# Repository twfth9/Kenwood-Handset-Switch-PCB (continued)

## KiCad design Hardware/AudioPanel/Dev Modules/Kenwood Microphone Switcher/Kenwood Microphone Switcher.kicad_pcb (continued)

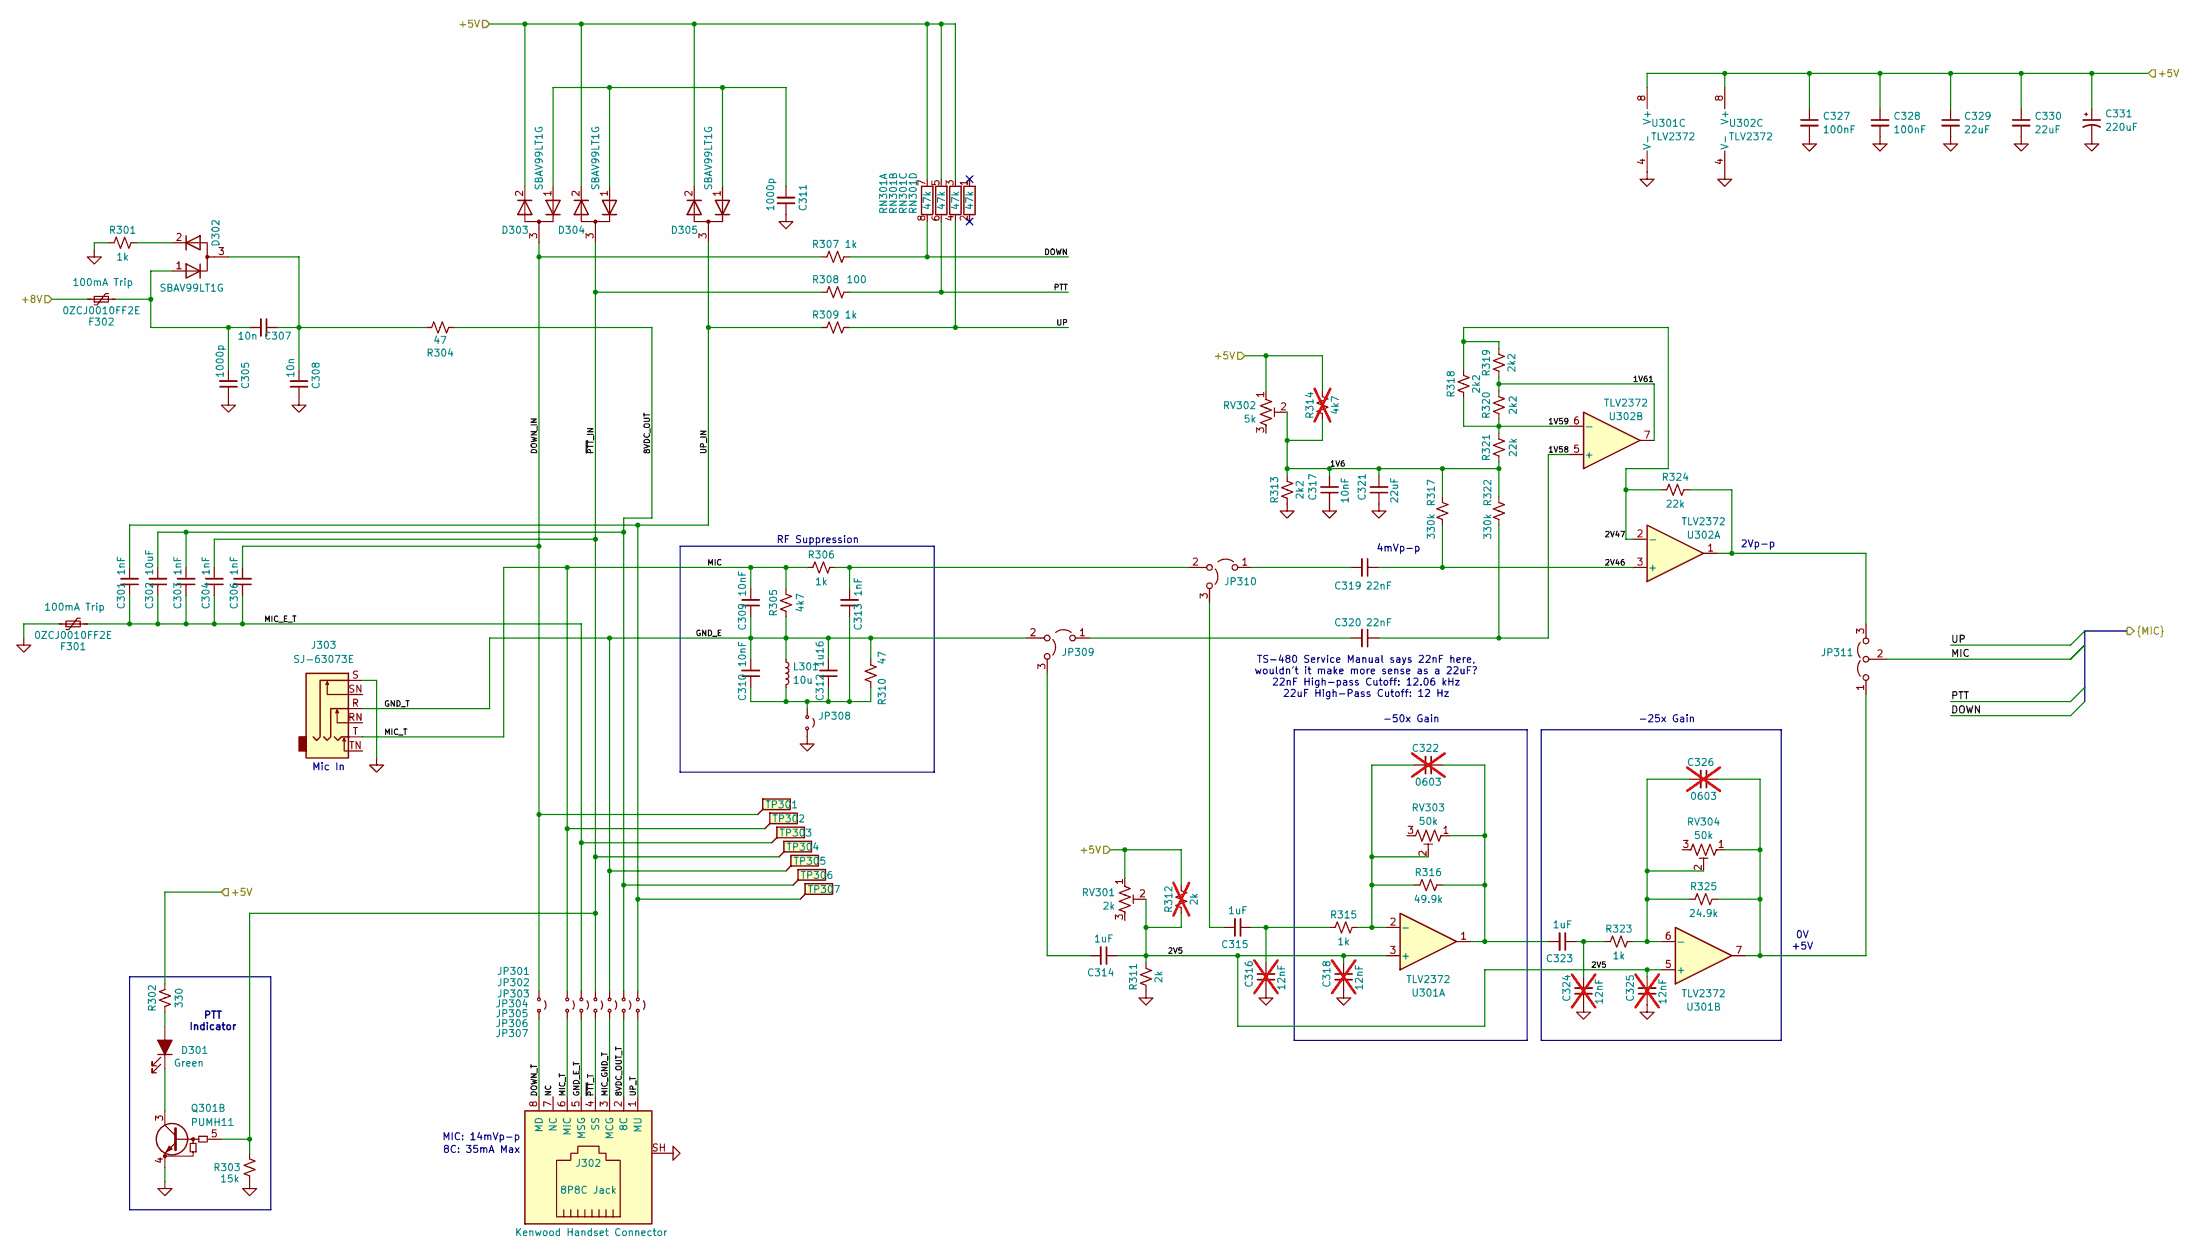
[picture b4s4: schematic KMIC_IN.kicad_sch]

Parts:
C301, C303, C304, C306, C313: 1nF; C_0402_1005Metric
C302: 10uF; C_0603_1608Metric
C305, C311: 1000p; C_0402_1005Metric
C307, C308: 10n; C_0402_1005Metric
C309, C310, C317: 10nF; C_0402_1005Metric
C312: 1u16; C_0603_1608Metric
C314, C315: 1uF; C_0603_1608Metric
C316, C318, C324, C325: 12nF; C_0402_1005Metric; not fitted
C319, C320: 22nF; C_0402_1005Metric
C321, C329, C330: 22uF; C_0603_1608Metric
C322, C326: 0603; C_0603_1608Metric; not fitted
C323: 1uF; C_0402_1005Metric
C327, C328: 100nF; C_0402_1005Metric
C331: 220uF; CP_Elec_10x10
D301: Green; LED_0603_1608Metric; DigiKey Part Number 732-5016-ND
D302, D303, D304, D305: SBAV99LT1G; SOT-23
F301, F302: 0ZCJ0010FF2E; Fuse_1206_3216Metric
J302: 8P8C Jack; Mystery_RJ45
J303: SJ-63073E; CUI_SJ-63073E
JP301, JP302, JP303, JP304, JP305, JP306, JP307, JP308: Jumper_2_Small_Open; SolderJumper-2_P1.3mm_Open_Pad1.0x1.5mm
JP309, JP310, JP311: Jumper_3_Open; SolderBridge_3L
L301: 10u; L_0805_2012Metric
Q301: PUMH11; SOT363_NXP
R301, R306, R307, R309, R315, R323: 1k; R_0402_1005Metric
R302: 330; R_0402_1005Metric
R303: 15k; R_0402_1005Metric
R304, R310: 47; R_0402_1005Metric
R305: 4k7; R_0402_1005Metric
R308: 100; R_0402_1005Metric
R311: 2k; R_0402_1005Metric
R312: 2k; R_0402_1005Metric; not fitted
R313, R318, R319, R320: 2k2; R_0402_1005Metric
R314: 4k7; R_0402_1005Metric; not fitted
R316: 49.9k; R_0402_1005Metric
R317, R322: 330k; R_0402_1005Metric
R321, R324: 22k; R_0402_1005Metric
R325: 24.9k; R_0402_1005Metric
RN301: 47k; R_Array_Convex_4x1206
RV301: 2k; Potentiometer_Bourns_TC33X_Vertical
RV302: 5k; Potentiometer_Bourns_TC33X_Vertical
RV303, RV304: 50k; Potentiometer_Bourns_TC33X_Vertical
TP301, TP302, TP303, TP304, TP305, TP306, TP307: TestPoint_Flag; KEYSTONE_5017
U301, U302: TLV2372; SOIC-8_3.9x4.9mm_P1.27mm

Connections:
/+5V_CODRIVER: C327.1, C328.1, C329.1, C330.1, C331.1, D303.2 (K), D304.2 (K), D305.2 (K), R302.2, R312.1, R314.1, RN301.3, RN301.5, RN301.7, RV301.1, RV302.1, U301.8 (V+), U302.8 (V+); also elsewhere on the board
/+8V_CODRIVER: F302.1; also elsewhere on the board
/CODRIVER_MIC.DOWN: R307.1, RN301.8
/CODRIVER_MIC.MIC: C309.2, J302.6 (MIC), J303.T, JP302.1 (A), JP302.2 (B), JP311.2 (C), R305.1, R306.2, TP302.1; also elsewhere on the board
/CODRIVER_MIC.PTT: R308.1, RN301.6; also elsewhere on the board
/CODRIVER_MIC.UP: R309.1, RN301.4; also elsewhere on the board
/CoDriver MIC Input/1V6: C317.2, C321.2, R313.1, R314.2, R317.1, R321.2, R322.1, RV302.2
/CoDriver MIC Input/1V58: C320.1, R322.2, U302.5 (+)
/CoDriver MIC Input/1V59: R318.2, R320.2, R321.1, U302.6 (-)
/CoDriver MIC Input/1V61: R319.2, R320.1, U302.7
/CoDriver MIC Input/2V5: C314.1, C318.2, C325.2, R311.1, R312.2, RV301.2, U301.3 (+), U301.5 (+)
/CoDriver MIC Input/2V46: C319.1, R317.2, U302.3 (+)
/CoDriver MIC Input/2V47: R318.1, R319.1, R324.2, U302.2 (-)
/CoDriver MIC Input/8VDC_OUT: C302.2, C303.2, JP306.1 (A), R304.2, TP306.1
/CoDriver MIC Input/8VDC_OUT_T: J302.2 (8C), JP306.2 (B)
/CoDriver MIC Input/DOWN_IN: C306.2, D303.3 (common), JP301.1 (A), R307.2, TP301.1
/CoDriver MIC Input/DOWN_T: J302.8 (MD), JP301.2 (B)
/CoDriver MIC Input/GND_E: C309.1, C310.2, C312.2, J303.R, JP305.1 (A), JP309.2 (C), L301.1, R305.2, R310.1, TP305.1
/CoDriver MIC Input/GND_E_T: J302.5 (MSG), JP303.2 (B)
/CoDriver MIC Input/MIC_E_T: C301.1, C302.1, C303.1, C304.1, C306.1, F301.2, JP303.1 (A), TP303.1
/CoDriver MIC Input/MIC_GND_T: J302.3 (MCG), JP305.2 (B)
/CoDriver MIC Input/NC: J302.7 (NC)
/CoDriver MIC Input/UP_IN: C301.2, D305.3 (common), JP307.1 (A), R309.2, TP307.1
/CoDriver MIC Input/UP_T: J302.1 (MU), JP307.2 (B)
/CoDriver MIC Input/~PTT_IN: C304.2, D304.3 (common), JP304.1 (A), Q301.5 (B2), R303.1, R308.2, TP304.1
/CoDriver MIC Input/~PTT_T: J302.4 (SS), JP304.2 (B)
/Driver MIC Input/~PTT_IN: Q301.2 (B1); also elsewhere on the board
GND: C305.1, C308.1, C311.1, C316.1, C317.1, C318.1, C321.1, C324.1, C325.1, C327.2, C328.2, C329.2, C330.2, C331.2, F301.1, J302.SH, J303.S, JP308.2 (B), Q301.1 (E1), Q301.4 (E2), R301.2, R303.2, R311.2, R313.2, U301.4 (V-), U302.4 (V-); also elsewhere on the board
unnamed: C315.1, C316.2, R315.2
unnamed: C322.1, C323.2, R316.1, RV303.1, U301.1
unnamed: C323.1, C324.2, R323.2
unnamed: D301.2 (A), R302.1
unnamed: D301.1 (K), Q301.3 (C2)
unnamed: C305.2, C307.2, D302.1 (A), F302.2
unnamed: D302.2 (K), R301.1
unnamed: C307.1, C308.2, D302.3 (common), R304.1
unnamed: C311.2, D303.1 (A), D304.1 (A), D305.1 (A)
unnamed 278: Q301.6 (C1); also elsewhere on the board
unnamed: C310.1, C312.1, C313.1, JP308.1 (A), L301.2, R310.2
unnamed: C320.2, JP309.1 (A)
unnamed: C314.2, JP309.3 (B)
unnamed: C319.2, JP310.1 (A)
unnamed: C315.2, JP310.3 (B)
unnamed: C313.2, JP310.2 (C), R306.1
unnamed: C326.1, JP311.1 (A), R325.1, RV304.1, U301.7
unnamed: JP311.3 (B), R324.1, U302.1
unnamed: C322.2, R315.1, R316.2, RV303.2, U301.2 (-)
unnamed: C326.2, R323.1, R325.2, RV304.2, U301.6 (-)

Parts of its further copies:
C401, C403, C404, C406, C413: 1nF; C_0402_1005Metric
C402: 10uF; C_0603_1608Metric
C405, C411: 1000p; C_0402_1005Metric
C407, C408: 10n; C_0402_1005Metric
C409, C410, C417: 10nF; C_0402_1005Metric
C412: 1u16; C_0603_1608Metric
C414, C415: 1uF; C_0603_1608Metric
C416, C418, C424, C425: 12nF; C_0402_1005Metric; not fitted
C419, C420: 22nF; C_0402_1005Metric
C421, C429, C430: 22uF; C_0603_1608Metric
C422, C426: 0603; C_0603_1608Metric; not fitted
C423: 1uF; C_0402_1005Metric
C427, C428: 100nF; C_0402_1005Metric
C431: 220uF; CP_Elec_10x10
D401: Green; LED_0603_1608Metric; DigiKey Part Number 732-5016-ND
D402, D403, D404, D405: SBAV99LT1G; SOT-23
F401, F402: 0ZCJ0010FF2E; Fuse_1206_3216Metric
J402: 8P8C Jack; Mystery_RJ45
J403: SJ-63073E; CUI_SJ-63073E
JP401, JP402, JP403, JP404, JP405, JP406, JP407, JP408: Jumper_2_Small_Open; SolderJumper-2_P1.3mm_Open_Pad1.0x1.5mm
JP409, JP410, JP411: Jumper_3_Open; SolderBridge_3L
L401: 10u; L_0805_2012Metric
R401, R406, R407, R409, R415, R423: 1k; R_0402_1005Metric
R402: 330; R_0402_1005Metric
R403: 15k; R_0402_1005Metric
R404, R410: 47; R_0402_1005Metric
R405: 4k7; R_0402_1005Metric
R408: 100; R_0402_1005Metric
R411: 2k; R_0402_1005Metric
R412: 2k; R_0402_1005Metric; not fitted
R413, R418, R419, R420: 2k2; R_0402_1005Metric
R414: 4k7; R_0402_1005Metric; not fitted
R416: 49.9k; R_0402_1005Metric
R417, R422: 330k; R_0402_1005Metric
R421, R424: 22k; R_0402_1005Metric
R425: 24.9k; R_0402_1005Metric
RN401: 47k; R_Array_Convex_4x1206
RV401: 2k; Potentiometer_Bourns_TC33X_Vertical
RV402: 5k; Potentiometer_Bourns_TC33X_Vertical
RV403, RV404: 50k; Potentiometer_Bourns_TC33X_Vertical
TP401, TP402, TP403, TP404, TP405, TP406, TP407: TestPoint_Flag; KEYSTONE_5017
U401, U402: TLV2372; SOIC-8_3.9x4.9mm_P1.27mm

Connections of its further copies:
/+5V_DRIVER: C427.1, C428.1, C429.1, C430.1, C431.1, D403.2 (K), D404.2 (K), D405.2 (K), R402.2, R412.1, R414.1, RN401.3, RN401.5, RN401.7, RV401.1, RV402.1, U401.8 (V+), U402.8 (V+); also elsewhere on the board
/+8V_DRIVER: F402.1; also elsewhere on the board
/DRIVER_MIC.DOWN: R407.1, RN401.8
/DRIVER_MIC.MIC: C409.2, J402.6 (MIC), J403.T, JP402.1 (A), JP402.2 (B), JP411.2 (C), R405.1, R406.2, TP402.1; also elsewhere on the board
/DRIVER_MIC.PTT: R408.1, RN401.6; also elsewhere on the board
/DRIVER_MIC.UP: R409.1, RN401.4; also elsewhere on the board
/Driver MIC Input/1V6: C417.2, C421.2, R413.1, R414.2, R417.1, R421.2, R422.1, RV402.2
/Driver MIC Input/1V58: C420.1, R422.2, U402.5 (+)
/Driver MIC Input/1V59: R418.2, R420.2, R421.1, U402.6 (-)
/Driver MIC Input/1V61: R419.2, R420.1, U402.7
/Driver MIC Input/2V5: C414.1, C418.2, C425.2, R411.1, R412.2, RV401.2, U401.3 (+), U401.5 (+)
/Driver MIC Input/2V46: C419.1, R417.2, U402.3 (+)
/Driver MIC Input/2V47: R418.1, R419.1, R424.2, U402.2 (-)
/Driver MIC Input/8VDC_OUT: C402.2, C403.2, JP406.1 (A), R404.2, TP406.1
/Driver MIC Input/8VDC_OUT_T: J402.2 (8C), JP406.2 (B)
/Driver MIC Input/DOWN_IN: C406.2, D403.3 (common), JP401.1 (A), R407.2, TP401.1
/Driver MIC Input/DOWN_T: J402.8 (MD), JP401.2 (B)
/Driver MIC Input/GND_E: C409.1, C410.2, C412.2, J403.R, JP405.1 (A), JP409.2 (C), L401.1, R405.2, R410.1, TP405.1
/Driver MIC Input/GND_E_T: J402.5 (MSG), JP403.2 (B)
/Driver MIC Input/MIC_E_T: C401.1, C402.1, C403.1, C404.1, C406.1, F401.2, JP403.1 (A), TP403.1
/Driver MIC Input/MIC_GND_T: J402.3 (MCG), JP405.2 (B)
/Driver MIC Input/NC: J402.7 (NC)
/Driver MIC Input/UP_IN: C401.2, D405.3 (common), JP407.1 (A), R409.2, TP407.1
/Driver MIC Input/UP_T: J402.1 (MU), JP407.2 (B)
/Driver MIC Input/~PTT_IN: C404.2, D404.3 (common), JP404.1 (A), R403.1, R408.2, TP404.1; also elsewhere on the board
/Driver MIC Input/~PTT_T: J402.4 (SS), JP404.2 (B)
GND: C405.1, C408.1, C411.1, C416.1, C417.1, C418.1, C421.1, C424.1, C425.1, C427.2, C428.2, C429.2, C430.2, C431.2, F401.1, J402.SH, J403.S, JP408.2 (B), R401.2, R403.2, R411.2, R413.2, U401.4 (V-), U402.4 (V-); also elsewhere on the board
unnamed: C415.1, C416.2, R415.2
unnamed: C422.1, C423.2, R416.1, RV403.1, U401.1
unnamed: C423.1, C424.2, R423.2
unnamed: D401.2 (A), R402.1
unnamed 278: D401.1 (K); also elsewhere on the board
unnamed: C405.2, C407.2, D402.1 (A), F402.2
unnamed: D402.2 (K), R401.1
unnamed: C407.1, C408.2, D402.3 (common), R404.1
unnamed: C411.2, D403.1 (A), D404.1 (A), D405.1 (A)
unnamed: C410.1, C412.1, C413.1, JP408.1 (A), L401.2, R410.2
unnamed: C420.2, JP409.1 (A)
unnamed: C414.2, JP409.3 (B)
unnamed: C419.2, JP410.1 (A)
unnamed: C415.2, JP410.3 (B)
unnamed: C413.2, JP410.2 (C), R406.1
unnamed: C426.1, JP411.1 (A), R425.1, RV404.1, U401.7
unnamed: JP411.3 (B), R424.1, U402.1
unnamed: C422.2, R415.1, R416.2, RV403.2, U401.2 (-)
unnamed: C426.2, R423.1, R425.2, RV404.2, U401.6 (-)

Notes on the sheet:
MIC: 14mVp-p
RF Suppression
-50x Gain
4mVp-p
PTT Indicator
-25x Gain
TS-480 Service Manual says 22nF here, wouldn't it make more sense as a 22uF? 22nF High-pass Cutoff: 12.06 kHz 22uF High-Pass Cutoff: 12 Hz
Mic In
0V +5V
8C: 35mA Max
2Vp-p

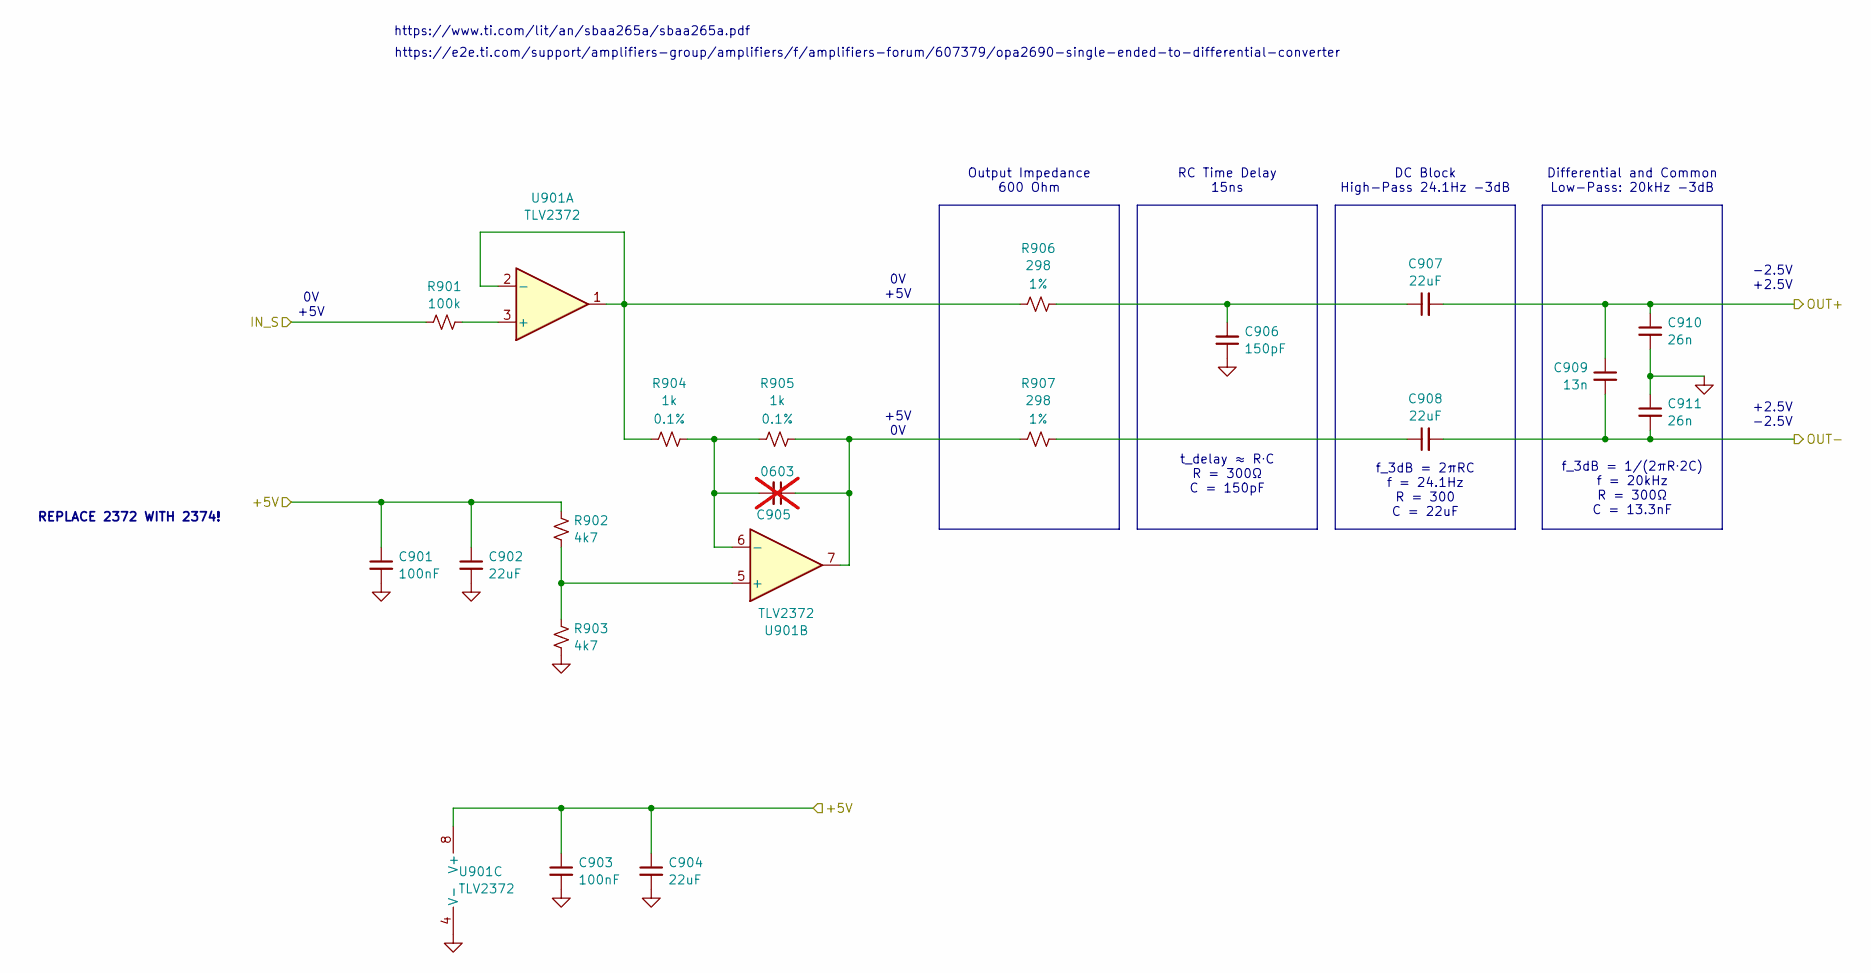
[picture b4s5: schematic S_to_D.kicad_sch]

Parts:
C901, C903: 100nF; C_0402_1005Metric
C902, C904, C907, C908: 22uF; C_0603_1608Metric
C905: 0603; C_0603_1608Metric; not fitted
C906: 150pF; C_0402_1005Metric
C909: 13n; C_0402_1005Metric
C910, C911: 26n; C_0402_1005Metric
R901: 100k; R_0402_1005Metric
R902, R903: 4k7; R_0402_1005Metric
R904, R905: 1k; R_0402_1005Metric; Tolerance 0.1%
R906, R907: 298; R_0402_1005Metric; Tolerance 1%
U901: TLV2372; SOIC-8_3.9x4.9mm_P1.27mm

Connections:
/+5V_MIC_480: C901.1, C902.1, C903.1, C904.1, R902.2, U901.8 (V+); also elsewhere on the board
/TS-480 MIC Output/MIC+: C907.2, C909.1, C910.1; also elsewhere on the board
/TS-480 MIC Output/MIC-: C908.2, C909.2, C911.2; also elsewhere on the board
/TS-480 MIC Output/Single to Differential/IN_S: R901.1; also elsewhere on the board
GND: C901.2, C902.2, C903.2, C904.2, C906.1, C910.2, C911.1, R903.1, U901.4 (V-); also elsewhere on the board
unnamed: C905.1, R905.2, R907.1, U901.7
unnamed: C906.2, C907.1, R906.2
unnamed: C908.1, R907.2
unnamed: R901.2, U901.3 (+)
unnamed: R904.1, R906.1, U901.1, U901.2 (-)
unnamed: R902.1, R903.2, U901.5 (+)
unnamed: C905.2, R904.2, R905.1, U901.6 (-)

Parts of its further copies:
C1001, C1003, C1101, C1103, C1201, C1203: 100nF; C_0402_1005Metric
C1002, C1004, C1007, C1008, C1102, C1104, C1107, C1108, C1202, C1204, C1207, C1208: 22uF; C_0603_1608Metric
C1005, C1105, C1205: 0603; C_0603_1608Metric; not fitted
C1006, C1106, C1206: 150pF; C_0402_1005Metric
C1009, C1109, C1209: 13n; C_0402_1005Metric
C1010, C1011, C1110, C1111, C1210, C1211: 26n; C_0402_1005Metric
R1001, R1101, R1201: 100k; R_0402_1005Metric
R1002, R1003, R1102, R1103, R1202, R1203: 4k7; R_0402_1005Metric
R1004, R1005, R1104, R1105, R1204, R1205: 1k; R_0402_1005Metric; Tolerance 0.1%
R1006, R1007, R1106, R1107, R1206, R1207: 298; R_0402_1005Metric; Tolerance 1%
U1001, U1101, U1201: TLV2372; SOIC-8_3.9x4.9mm_P1.27mm

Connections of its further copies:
/+5V_MIC_700: C1101.1, C1102.1, C1103.1, C1104.1, R1102.2, U1101.8 (V+); also elsewhere on the board
/+5V_MIC_710: C1001.1, C1002.1, C1003.1, C1004.1, R1002.2, U1001.8 (V+); also elsewhere on the board
/+5V_MIC_EXTRA: C1201.1, C1202.1, C1203.1, C1204.1, R1202.2, U1201.8 (V+); also elsewhere on the board
/D-700 MIC Output/MIC+: C1107.2, C1109.1, C1110.1; also elsewhere on the board
/D-700 MIC Output/MIC-: C1108.2, C1109.2, C1111.2; also elsewhere on the board
/D-700 MIC Output/Single to Differential/IN_S: R1101.1; also elsewhere on the board
/D-710 MIC Output/MIC+: C1007.2, C1009.1, C1010.1; also elsewhere on the board
/D-710 MIC Output/MIC-: C1008.2, C1009.2, C1011.2; also elsewhere on the board
/D-710 MIC Output/Single to Differential/IN_S: R1001.1; also elsewhere on the board
/EXTRA MIC Output/MIC+: C1207.2, C1209.1, C1210.1; also elsewhere on the board
/EXTRA MIC Output/MIC-: C1208.2, C1209.2, C1211.2; also elsewhere on the board
/EXTRA MIC Output/Single to Differential/IN_S: R1201.1; also elsewhere on the board
GND: C1001.2, C1002.2, C1003.2, C1004.2, C1006.1, C1010.2, C1011.1, C1101.2, C1102.2, C1103.2, C1104.2, C1106.1, C1110.2, C1111.1, C1201.2, C1202.2, C1203.2, C1204.2, C1206.1, C1210.2, C1211.1, R1003.1, R1103.1, R1203.1, U1001.4 (V-), U1101.4 (V-), U1201.4 (V-); also elsewhere on the board
unnamed: C1005.1, R1005.2, R1007.1, U1001.7
unnamed: C1006.2, C1007.1, R1006.2
unnamed: C1008.1, R1007.2
unnamed: C1105.1, R1105.2, R1107.1, U1101.7
unnamed: C1106.2, C1107.1, R1106.2
unnamed: C1108.1, R1107.2
unnamed: C1205.1, R1205.2, R1207.1, U1201.7
unnamed: C1206.2, C1207.1, R1206.2
unnamed: C1208.1, R1207.2
unnamed: R1001.2, U1001.3 (+)
unnamed: R1004.1, R1006.1, U1001.1, U1001.2 (-)
unnamed: R1002.1, R1003.2, U1001.5 (+)
unnamed: C1005.2, R1004.2, R1005.1, U1001.6 (-)
unnamed: R1101.2, U1101.3 (+)
unnamed: R1104.1, R1106.1, U1101.1, U1101.2 (-)
unnamed: R1102.1, R1103.2, U1101.5 (+)
unnamed: C1105.2, R1104.2, R1105.1, U1101.6 (-)
unnamed: R1201.2, U1201.3 (+)
unnamed: R1204.1, R1206.1, U1201.1, U1201.2 (-)
unnamed: R1202.1, R1203.2, U1201.5 (+)
unnamed: C1205.2, R1204.2, R1205.1, U1201.6 (-)

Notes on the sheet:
+2.5V -2.5V
DC Block High-Pass 24.1Hz -3dB
0V +5V
https://www.ti.com/lit/an/sbaa265a/sbaa265a.pdf
t_delay ≈ R⋅C R = 300Ω C = 150pF
https://e2e.ti.com/support/amplifiers-group/amplifiers/f/amplifiers-forum/607379/opa2690-single-ended-to-differential-converter
RC Time Delay 15ns
Output Impedance 600 Ohm
f_3dB = 2πRC f = 24.1Hz R = 300 C = 22uF
Differential and Common Low-Pass: 20kHz -3dB
+5V 0V
REPLACE 2372 WITH 2374!
-2.5V +2.5V
f_3dB = 1/(2πR⋅2C) f = 20kHz R = 300Ω C = 13.3nF

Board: 2 copper layers, 730 parts (0 on the bottom side), 387 nets, no tracks yet.

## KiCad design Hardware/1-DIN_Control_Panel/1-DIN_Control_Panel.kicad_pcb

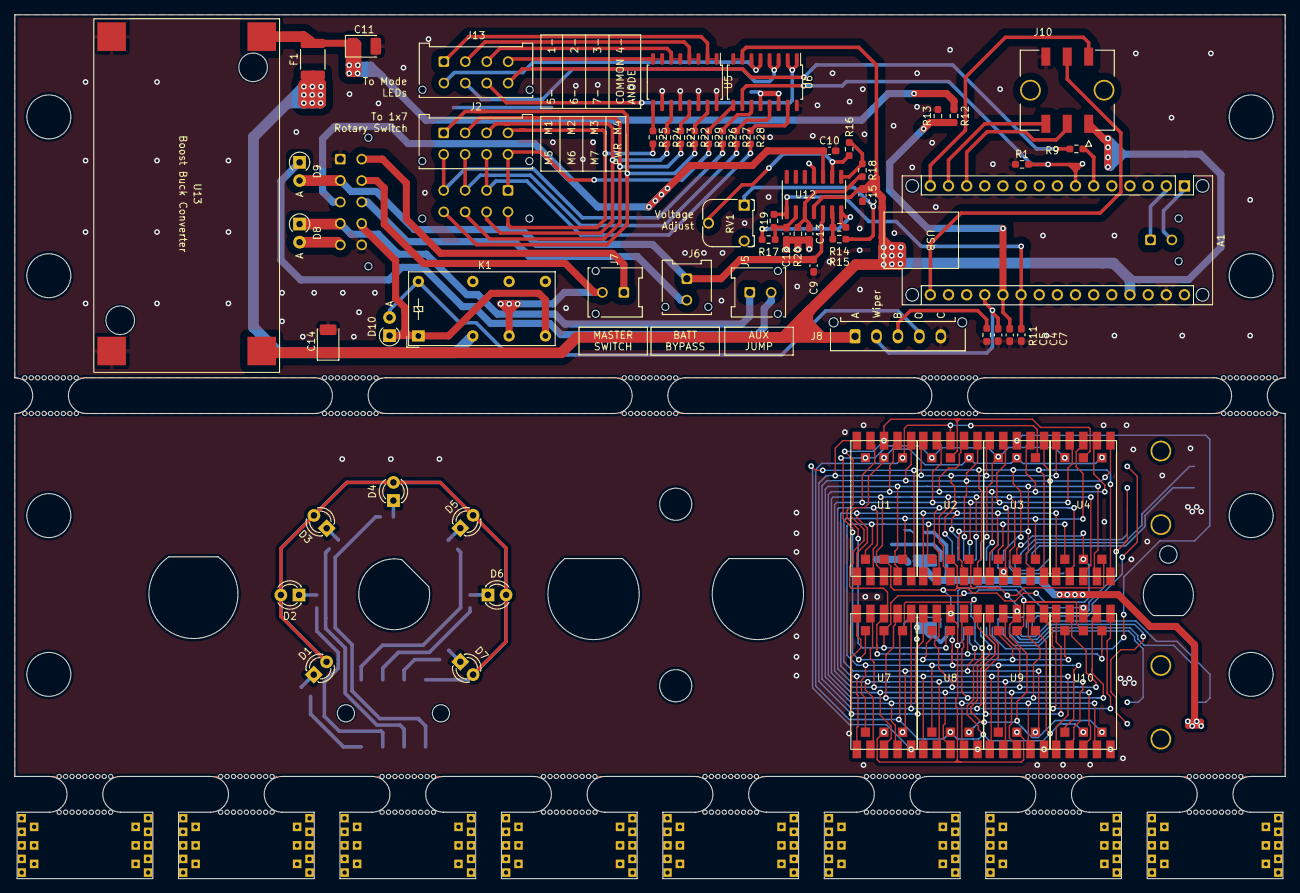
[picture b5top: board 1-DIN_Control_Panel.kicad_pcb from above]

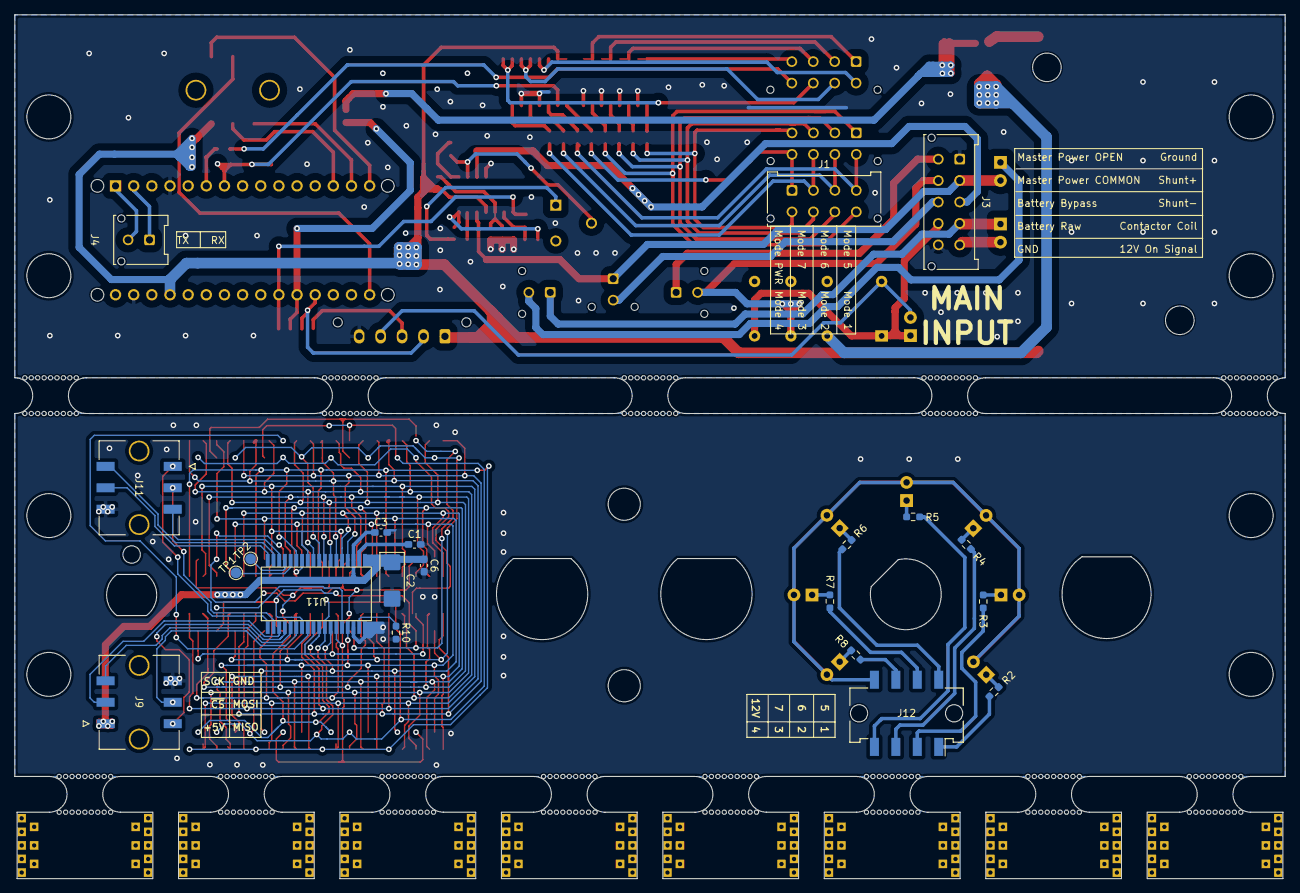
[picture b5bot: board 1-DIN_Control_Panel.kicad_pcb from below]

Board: 2 copper layers, 177.8 x 120.9 mm, 97 parts (21 on the bottom side), 104 nets.

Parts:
A1: Arduino Nano; Arduino_Nano_WithMountingHoles
C1: 22pF; C_0603_1608Metric_Pad1.08x0.95mm_HandSolder
C2: 47µF; CP_EIA-6032-28_Kemet-C_Pad2.25x2.35mm_HandSolder
C3, C4, C5, C6, C7, C9, C10, C15: 100nF; C_0603_1608Metric_Pad1.08x0.95mm_HandSolder
C11: 10µF; CP_EIA-3528-21_Kemet-B_Pad1.50x2.35mm_HandSolder
C12, C13: DNP; C_0603_1608Metric_Pad1.08x0.95mm_HandSolder
C14: 22µF; CP_EIA-3528-21_Kemet-B_Pad1.50x2.35mm_HandSolder
D1, D2, D3, D4, D5, D6, D7: LED_Filled; LED_D3.0mm
D8, D9, D10: D; D_A-405_P2.54mm_Vertical_AnodeUp
F1: 1A Trip; Fuse_1812_4532Metric_Pad1.30x3.40mm_HandSolder
J1: Selector Knob Connector; Molex_Micro-Fit_3.0_43045-0812_2x04_P3.00mm_Vertical
J2: Rotary Switch 1x7; Molex_Micro-Fit_3.0_43045-0812_2x04_P3.00mm_Vertical
J3: 2x05 Molex Micro-Fit 3.0 43045; Molex_Micro-Fit_3.0_43045-1012_2x05_P3.00mm_Vertical
J4: UART Expansion; Molex_Micro-Fit_3.0_43045-0212_2x01_P3.00mm_Vertical
J5: SW - Aux Jump-Start; Molex_Micro-Fit_3.0_43045-0212_2x01_P3.00mm_Vertical
J6: SW - Battery Bypass; Molex_Micro-Fit_3.0_43045-0212_2x01_P3.00mm_Vertical
J7: SW - Master Power; Molex_Micro-Fit_3.0_43045-0212_2x01_P3.00mm_Vertical
J8: Pot/SW - Brightness; Molex_Micro-Fit_3.0_43650-0515_1x05_P3.00mm_Vertical
J9, J10, J11: 2x05 Molex Micro-Fit 3.0 43045; MOLEX_430450615
J12: Display LEDs; Molex_Micro-Fit_3.0_43045-0815_2x04_P3.00mm_Vertical
J13: Mode LEDs; Molex_Micro-Fit_3.0_43045-0812_2x04_P3.00mm_Vertical
K1: FINDER-40.52; Relay_DPDT_Finder_30.22
R1, R11, R13: 10kΩ; R_0603_1608Metric_Pad0.98x0.95mm_HandSolder
R2, R3, R4, R5, R6, R7, R8: 150Ω; R_0603_1608Metric_Pad0.98x0.95mm_HandSolder
R9: 0Ω or Bridge; R_0603_1608Metric_Pad0.98x0.95mm_HandSolder
R10: 56kΩ; R_0603_1608Metric_Pad0.98x0.95mm_HandSolder
R12: 22kΩ; R_0603_1608Metric_Pad0.98x0.95mm_HandSolder
R14, R16, R17, R18, R19, R20: 100kΩ; R_0603_1608Metric_Pad0.98x0.95mm_HandSolder
R15: 2.7kΩ; R_0603_1608Metric_Pad0.98x0.95mm_HandSolder
R22, R23, R24, R25, R26, R27, R28, R29: 39kΩ; R_0603_1608Metric_Pad0.98x0.95mm_HandSolder
RV1: 500Ω; Potentiometer_Runtron_RM-065_Vertical
TP1, TP2: TestPoint_Flag; TestPoint_Pad_D1.5mm
U1, U2, U3, U4, U7, U8, U9, U10: XZFAVG10
U5, U6: MMPQ3904; SOIC-16_4.55x10.3mm_P1.27mm
U11: MAX 6954 - SSOP; MAX6954-SSOP
U12: LM324DR; SOIC-14_3.9x8.7mm_P1.27mm
U13: 12V->5V Variable Boost Buck Converter; BoostBuck
mouse-bite-5mm-slot, mouse-bite-5mm-slot#2, mouse-bite-5mm-slot#3, mouse-bite-5mm-slot#4, mouse-bite-5mm-slot#5, mouse-bite-5mm-slot#6, mouse-bite-5mm-slot#7, mouse-bite-5mm-slot#8, mouse-bite-5mm-slot#9, mouse-bite-5mm-slot#10, mouse-bite-5mm-slot#11, mouse-bite-5mm-slot#12, mouse-bite-5mm-slot#13: VAL**; mouse-bite-5mm-slot

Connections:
+5V: A1.27 (+5V), C2.1, C3.1, C6.1, C14.1, C15.1, J8.1 (A), J9.1, J10.1, U6.7 (C4), U6.8 (C4), U11.19 (V+), U11.21 (V+), U12.4 (V+), U13.3 (+VOUT)
/Back Board/12V_ON: D8.2 (A), J3.5
/Back Board/Arduino_MISO: A1.15 (D12), J10.4
/Back Board/Arduino_MOSI: A1.14 (D11), J10.3
/Back Board/Arduino_SCK: A1.16 (D13), J10.5
/Back Board/Arduino_~CS: A1.13 (D10), J10.2
/Back Board/BATT_BYPASS: J3.8, J6.2
/Back Board/BATT_RAW: D10.1 (K), J3.9, K1.14, K1.A1
/Back Board/BRIGHTNESS_CONTROL: A1.19 (A0), C5.1, J8.2 (Wiper)
/Back Board/CONTACTOR_COIL: D8.1 (K), J3.4, J5.1
/Back Board/CURRENT_SENSE: A1.21 (A2), C7.1, R19.2, U12.1
/Back Board/MASTER_COMMON: J3.7, J7.2, K1.12
/Back Board/MASTER_OPEN: J3.6, J7.1
/Back Board/MODE_1: J1.8, J2.1, R22.2
/Back Board/MODE_1_LED: J13.1, U5.1 (C1), U5.2 (C1)
/Back Board/MODE_2: J1.7, J2.2, R23.2
/Back Board/MODE_2_LED: J13.2, U5.3 (C2), U5.4 (C2)
/Back Board/MODE_3: J1.6, J2.3, R24.2
/Back Board/MODE_3_LED: J13.3, U5.5 (C4), U5.6 (C3)
/Back Board/MODE_4: J1.5, J2.4, R25.2
/Back Board/MODE_4_LED: J13.4, U5.7 (C4), U5.8 (C4)
/Back Board/MODE_5: J1.4, J2.5, R26.2
/Back Board/MODE_5_LED: J13.5, U6.5 (C4), U6.6 (C3)
/Back Board/MODE_6: J1.3, J2.6, R27.2
/Back Board/MODE_6_LED: J13.6, U6.3 (C2), U6.4 (C2)
/Back Board/MODE_7: J1.2, J2.7, R28.2
/Back Board/MODE_7_LED: J13.7, U6.1 (C1), U6.2 (C1)
/Back Board/MODE_12V: J1.1, J2.8, R29.2
/Back Board/MODE_LED_BRIGHTNESS: A1.6 (D3), R9.1
/Back Board/MODE_PWR_DETECT: A1.7 (D4), R1.2, U6.10 (E4)
/Back Board/RX-EXPANSION: A1.2 (D0/RX), J4.1
/Back Board/SHUNT+: C9.1, D9.2 (A), J3.2, J6.1, U12.5 (+)
/Back Board/SHUNT-: C10.1, J3.3, U12.10 (+)
/Back Board/TX-EXPANSION: A1.1 (D1/TX), J4.2
/Back Board/VOLTAGE_SENSE: A1.20 (A1), C4.1, R12.1, R13.2
/Back Board/VOLT_SOURCE_SELECT: D10.2 (A), J8.4 (Open), K1.A2
/Front Board/6954_O0: U1.14 (CC), U2.10 (a), U4.10 (a), U7.10 (a), U8.10 (a), U9.10 (a), U10.10 (a), U11.7 (O0)
/Front Board/6954_O1: U3.14 (CC), U11.8 (O1)
/Front Board/6954_O2: U1.10 (a), U2.11 (b), U3.10 (a), U4.11 (b), U7.14 (CC), U8.11 (b), U10.11 (b), U11.9 (O2)
/Front Board/6954_O3: U2.6 (c), U4.6 (c), U8.6 (c), U9.14 (CC), U10.6 (c), U11.10 (O3)
/Front Board/6954_O4: U1.11 (b), U2.14 (CC), U3.11 (b), U7.11 (b), U8.7 (d), U9.11 (b), U10.7 (d), U11.11 (O4)
/Front Board/6954_O5: U1.6 (c), U3.6 (c), U4.14 (CC), U7.6 (c), U9.6 (c), U11.12 (O5)
/Front Board/6954_O6: U1.7 (d), U2.7 (d), U3.7 (d), U4.7 (d), U7.7 (d), U8.14 (CC), U9.7 (d), U11.13 (O6)
/Front Board/6954_O7: U10.14 (CC), U11.14 (O7)
/Front Board/6954_O8: U1.8 (e), U2.8 (e), U3.8 (e), U4.8 (e), U7.8 (e), U8.8 (e), U9.8 (e), U10.8 (e), U11.15 (O8)
/Front Board/6954_O9: U1.16 (f), U2.16 (f), U3.16 (f), U4.16 (f), U7.16 (f), U8.16 (f), U9.16 (f), U10.16 (f), U11.22 (O9)
/Front Board/6954_O10: U1.1 (g1(p)), U2.1 (g1(p)), U3.1 (g1(p)), U4.1 (g1(p)), U7.1 (g1(p)), U8.1 (g1(p)), U9.1 (g1(p)), U10.1 (g1(p)), U11.23 (O10)
/Front Board/6954_O11: U1.12 (g2(k)), U2.12 (g2(k)), U3.12 (g2(k)), U4.12 (g2(k)), U7.12 (g2(k)), U8.12 (g2(k)), U9.12 (g2(k)), U10.12 (g2(k)), U11.24 (O11)
/Front Board/6954_O12: U1.15 (h), U2.15 (h), U3.15 (h), U4.15 (h), U7.15 (h), U8.15 (h), U9.15 (h), U10.15 (h), U11.25 (O12)
/Front Board/6954_O13: U1.3 (i(m)), U2.3 (i(m)), U3.3 (i(m)), U4.3 (i(m)), U7.3 (i(m)), U8.3 (i(m)), U9.3 (i(m)), U10.3 (i(m)), U11.26 (O13)
/Front Board/6954_O14: U1.9 (j(g)), U2.9 (j(g)), U3.9 (j(g)), U4.9 (j(g)), U7.9 (j(g)), U8.9 (j(g)), U9.9 (j(g)), U10.9 (j(g)), U11.27 (O14)
/Front Board/6954_O15: U1.13 (k(j)), U2.13 (k(j)), U3.13 (k(j)), U4.13 (k(j)), U7.13 (k(j)), U8.13 (k(j)), U9.13 (k(j)), U10.13 (k(j)), U11.28 (O15)
/Front Board/6954_O16: U1.4 (l), U2.4 (l), U3.4 (l), U4.4 (l), U7.4 (l), U8.4 (l), U9.4 (l), U10.4 (l), U11.29 (O16)
/Front Board/6954_O17: U1.2 (m(n)), U2.2 (m(n)), U3.2 (m(n)), U4.2 (m(n)), U7.2 (m(n)), U8.2 (m(n)), U9.2 (m(n)), U10.2 (m(n)), U11.30 (O17)
/Front Board/6954_O18: U1.5 (DP), U2.5 (DP), U3.5 (DP), U4.5 (DP), U7.5 (DP), U8.5 (DP), U9.5 (DP), U10.5 (DP), U11.31 (O18)
/Front Board/MISO: J9.4, U11.4 (DOUT)
/Front Board/MOSI: J9.5, U11.6 (DIN)
/Front Board/SCK: J9.3, U11.5 (CLK)
/Front Board/~CS: J9.2, U11.3 (~CS)
GND: A1.4 (GND), A1.29 (GND), C1.2, C2.2, C3.2, C4.2, C5.2, C6.2, C7.2, C9.2, C10.2, C11.2, C12.2, C13.2, C14.2, C15.2, J3.1, J3.10, J8.5 (Common), J9.6, J10.6, J11.6, R1.1, R10.1, R11.1, R13.1, R20.2, U5.10 (E4), U5.12 (E3), U5.14 (E2), U5.16 (E1), U6.12 (E3), U6.14 (E2), U6.16 (E1), U11.16 (GND), U11.18 (GND), U12.11 (V-), U13.2 (-VIN), U13.4 (-VOUT)
unnamed: D1.2 (A), D2.2 (A), D3.2 (A), D4.2 (A), D5.2 (A), D6.2 (A), D7.2 (A), J12.8
unnamed: D1.1 (K), R2.2
unnamed: D2.1 (K), R3.2
unnamed: D3.1 (K), R4.2
unnamed: D4.1 (K), R5.2
unnamed: D5.1 (K), R6.2
unnamed: D6.1 (K), R7.2
unnamed: D7.1 (K), R8.2
unnamed: D9.1 (K), J5.2
unnamed: F1.1, K1.11
unnamed: J8.3 (B), R11.2
unnamed: J11.1, U11.1 (P0)
unnamed: J11.2, U11.2 (P1)
unnamed: J11.3, U11.34 (P2)
unnamed: J11.4, U11.35 (P3)
unnamed: J11.5, U11.36 (P4)
unnamed: J12.1, R2.1
unnamed: J12.2, R3.1
unnamed: J12.3, R4.1
unnamed: J12.4, R5.1
unnamed: J12.5, R6.1
unnamed: J12.6, R7.1
unnamed: J12.7, R8.1
unnamed: J13.8, R9.2
unnamed: R14.2, R17.1, U12.7
unnamed: R15.1, RV1.1
unnamed: R16.1, R18.1, U12.8
unnamed: R22.1, U5.15 (B1)
unnamed: R23.1, U5.13 (B2)
unnamed: R24.1, U5.11 (B3)
unnamed: R25.1, U5.9 (B4)
unnamed: R28.1, U6.15 (B1)
unnamed: R27.1, U6.13 (B2)
unnamed: R26.1, U6.11 (B3)
unnamed: R29.1, U6.9 (B4)
unnamed: TP1.1, U11.32 (BLINK)
unnamed: R10.2, U11.17 (ISET)
unnamed: C1.1, U11.20 (OSC)
unnamed: TP2.1, U11.33 (OSC_OUT)
unnamed: C13.1, R18.2, R20.1, U12.3 (+)
unnamed: C12.1, R17.2, R19.1, U12.2 (-)
unnamed: R14.1, R15.2, U12.6 (-)
unnamed: R16.2, RV1.2, U12.9 (-)
VCC: C11.1, F1.2, R12.2, U13.1 (+VIN)
